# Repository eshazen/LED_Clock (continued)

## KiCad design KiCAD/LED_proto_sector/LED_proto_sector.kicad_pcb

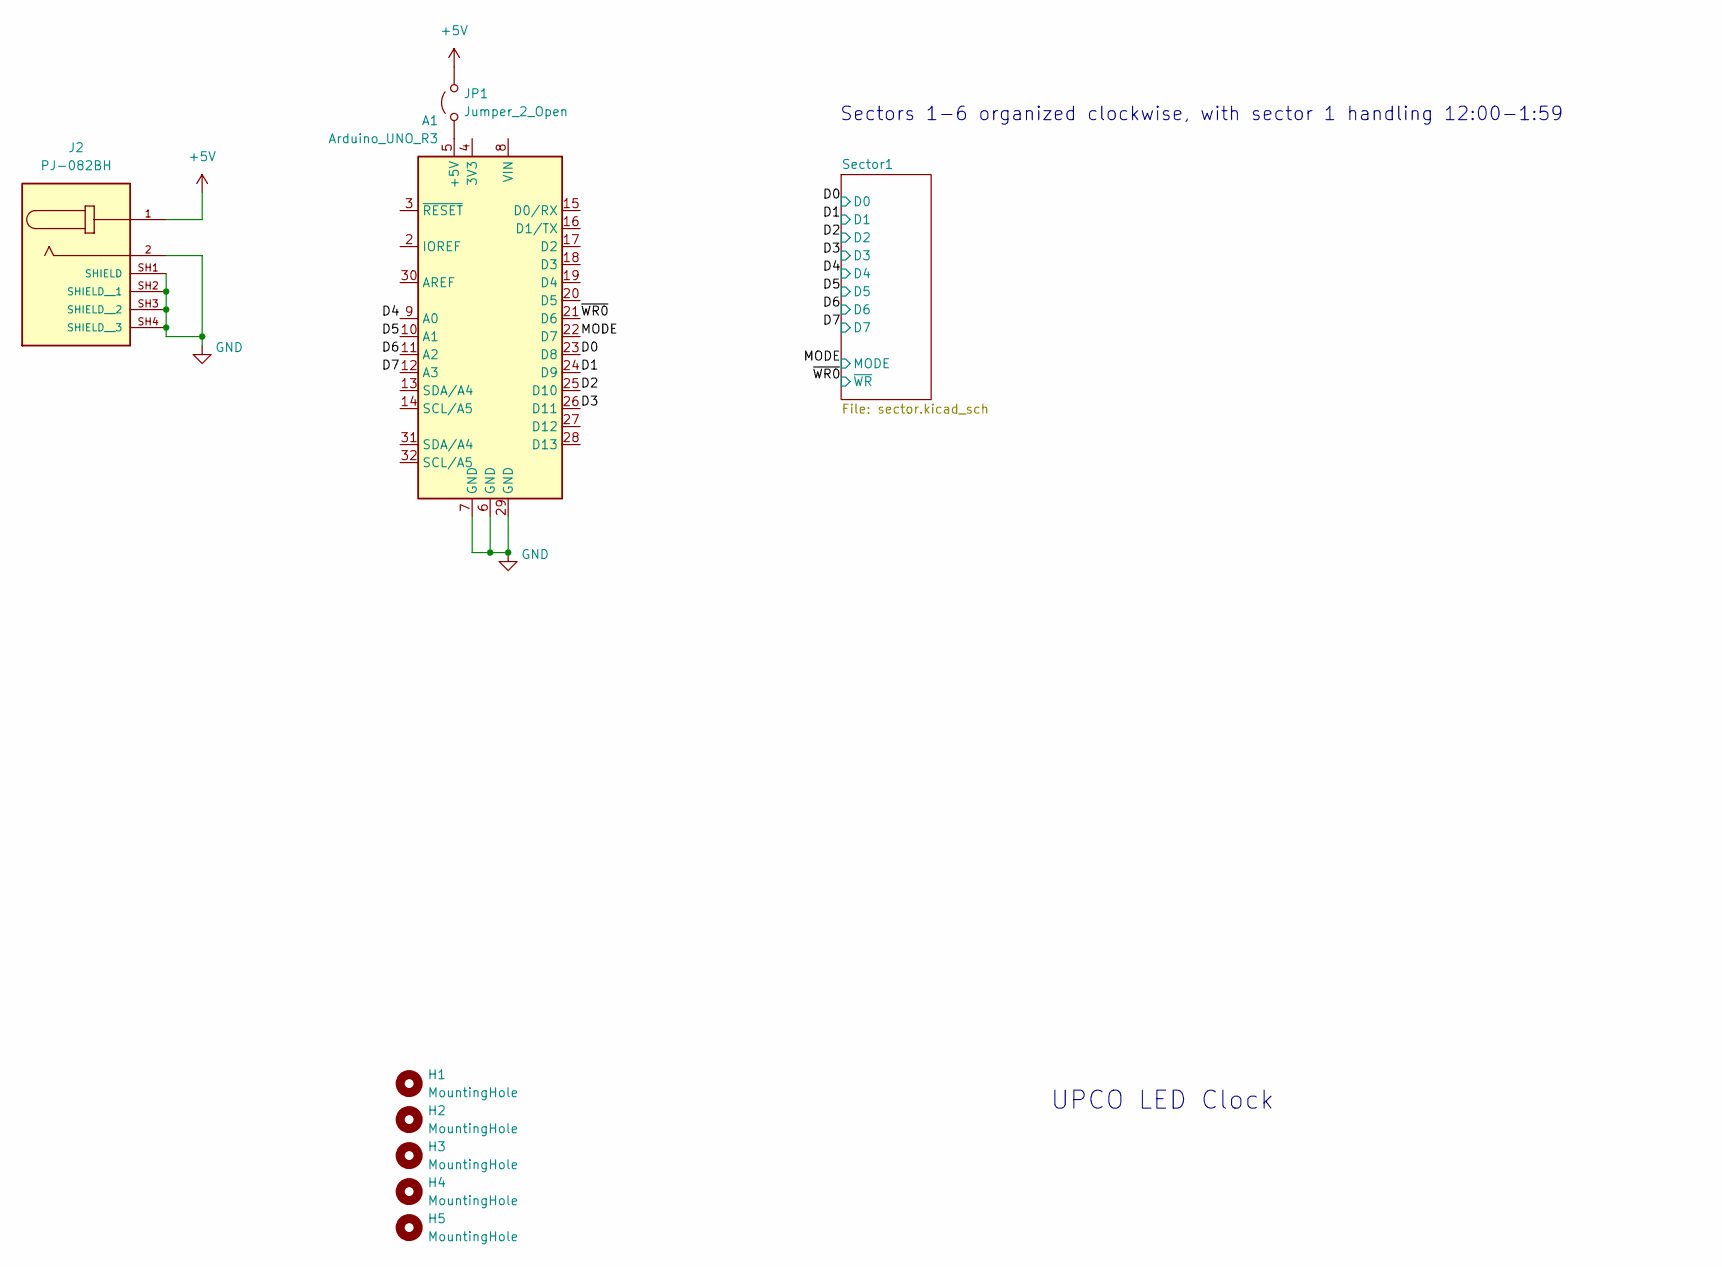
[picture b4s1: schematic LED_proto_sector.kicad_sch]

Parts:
A1: Arduino_UNO_R3
H1, H2, H3, H4, H5: MountingHole; MountingHole_4.3mm_M4
J2: PJ-082BH; SAMESKY_PJ-082BH; PARTREV 1.06
JP1: Jumper_2_Open; PinHeader_1x02_P2.54mm_Vertical

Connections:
+5V: J2.1, JP1.2 (B); also elsewhere on the board
/D0: A1.23 (D8); also elsewhere on the board
/D1: A1.24 (D9); also elsewhere on the board
/D2: A1.25 (D10); also elsewhere on the board
/D3: A1.26 (D11); also elsewhere on the board
/D4: A1.9 (A0); also elsewhere on the board
/D5: A1.10 (A1); also elsewhere on the board
/D6: A1.11 (A2); also elsewhere on the board
/D7: A1.12 (A3); also elsewhere on the board
/MODE: A1.22 (D7); also elsewhere on the board
/~WR0: A1.21 (D6); also elsewhere on the board
GND: A1.6 (GND), A1.7 (GND), A1.29 (GND), J2.2, J2.SH1 (SHIELD), J2.SH2 (SHIELD__1), J2.SH3 (SHIELD__2), J2.SH4 (SHIELD__3); also elsewhere on the board
unnamed: A1.5 (+5V), JP1.1 (A)

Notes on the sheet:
Sectors 1-6 organized clockwise, with sector 1 handling 12:00-1:59
UPCO LED Clock

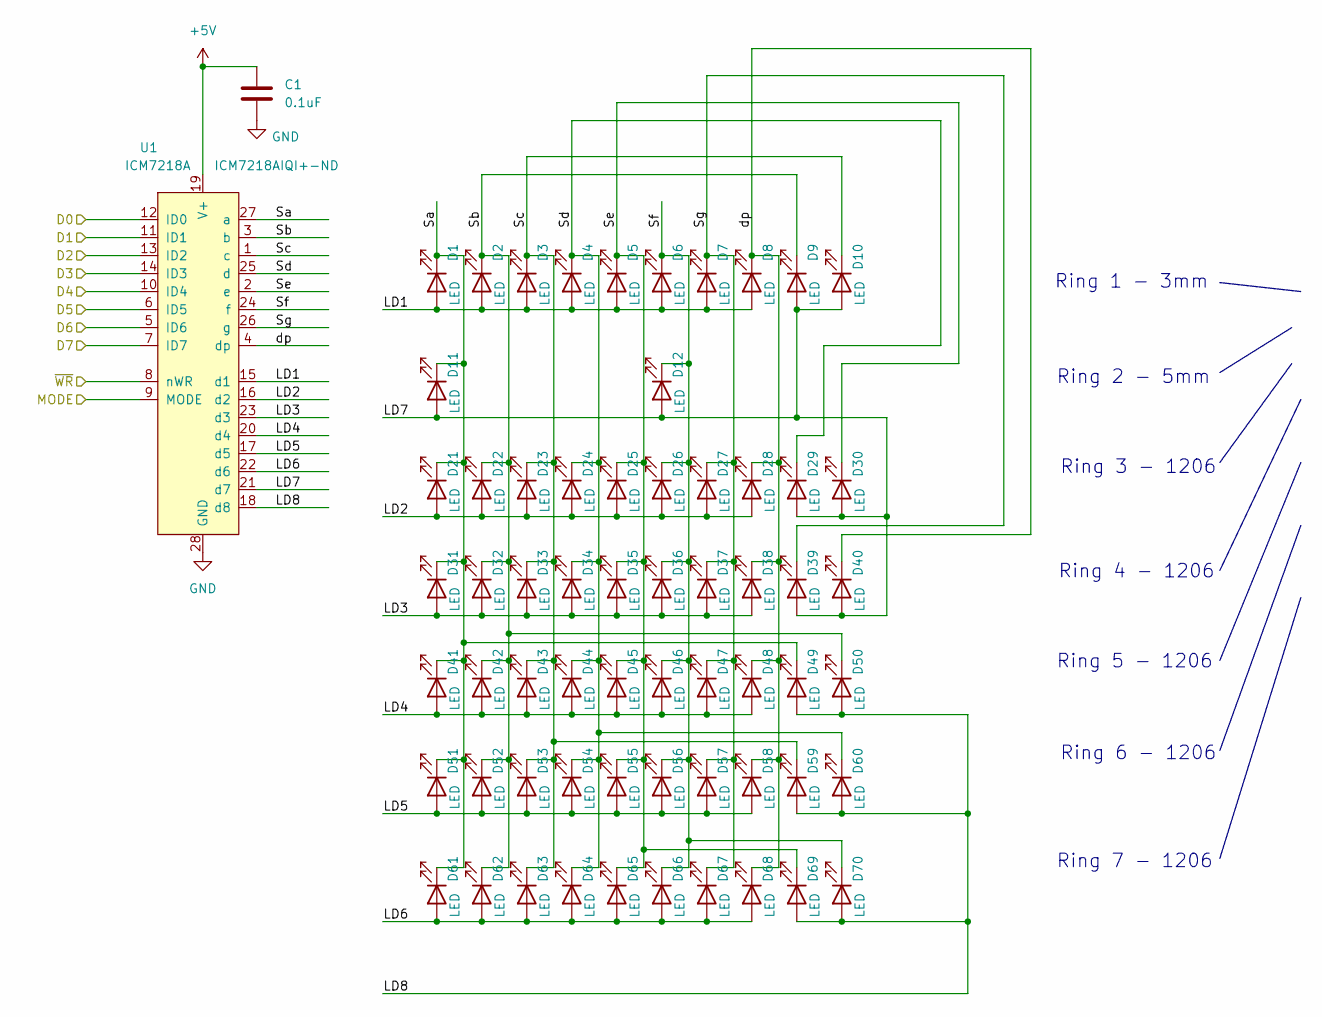
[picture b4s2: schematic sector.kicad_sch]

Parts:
C1: 0.1uF; C_1206_3216Metric_Pad1.33x1.80mm_HandSolder
D1, D2, D3, D4, D5, D6, D7, D8, D9, D10: LED; LED_D3.0mm
D11, D12: LED; LED_D5.0mm
D21, D22, D23, D24, D25, D26, D27, D28, D29, D30, D31, D32, D33, D34, D35, D36, D37, D38, D39, D40, D41, D42, D43, D44, D45, D46, D47, D48, D49, D50, D51, D52, D53, D54, D55, D56, D57, D58, D59, D60, D61, D62, D63, D64, D65, D66, D67, D68, D69, D70: LED; LED_1206_3216Metric_Pad1.42x1.75mm_HandSolder
U1: ICM7218A; DIP-28_W15.24mm_LongPads; DigiKey ICM7218AIQI+-ND

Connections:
+5V: C1.1, U1.19 (V+); also elsewhere on the board
/D0: U1.12 (ID0); also elsewhere on the board
/D1: U1.11 (ID1); also elsewhere on the board
/D2: U1.13 (ID2); also elsewhere on the board
/D3: U1.14 (ID3); also elsewhere on the board
/D4: U1.10 (ID4); also elsewhere on the board
/D5: U1.6 (ID5); also elsewhere on the board
/D6: U1.5 (ID6); also elsewhere on the board
/D7: U1.7 (ID7); also elsewhere on the board
/MODE: U1.9 (MODE); also elsewhere on the board
/Sector1/LD1: D1.2 (A), D2.2 (A), D3.2 (A), D4.2 (A), D5.2 (A), D6.2 (A), D7.2 (A), D8.2 (A), U1.15 (d1)
/Sector1/LD2: D21.2 (A), D22.2 (A), D23.2 (A), D24.2 (A), D25.2 (A), D26.2 (A), D27.2 (A), D28.2 (A), U1.16 (d2)
/Sector1/LD3: D31.2 (A), D32.2 (A), D33.2 (A), D34.2 (A), D35.2 (A), D36.2 (A), D37.2 (A), D38.2 (A), U1.23 (d3)
/Sector1/LD4: D41.2 (A), D42.2 (A), D43.2 (A), D44.2 (A), D45.2 (A), D46.2 (A), D47.2 (A), D48.2 (A), U1.20 (d4)
/Sector1/LD5: D51.2 (A), D52.2 (A), D53.2 (A), D54.2 (A), D55.2 (A), D56.2 (A), D57.2 (A), D58.2 (A), U1.17 (d5)
/Sector1/LD6: D61.2 (A), D62.2 (A), D63.2 (A), D64.2 (A), D65.2 (A), D66.2 (A), D67.2 (A), D68.2 (A), U1.22 (d6)
/Sector1/LD7: D9.2 (A), D10.2 (A), D11.2 (A), D12.2 (A), D29.2 (A), D30.2 (A), D39.2 (A), D40.2 (A), U1.21 (d7)
/Sector1/LD8: D49.2 (A), D50.2 (A), D59.2 (A), D60.2 (A), D69.2 (A), D70.2 (A), U1.18 (d8)
/Sector1/Sa: D1.1 (K), D11.1 (K), D21.1 (K), D31.1 (K), D41.1 (K), D49.1 (K), D51.1 (K), D61.1 (K), U1.27 (a)
/Sector1/Sb: D2.1 (K), D9.1 (K), D22.1 (K), D32.1 (K), D42.1 (K), D50.1 (K), D52.1 (K), D62.1 (K), U1.3 (b)
/Sector1/Sc: D3.1 (K), D10.1 (K), D23.1 (K), D33.1 (K), D43.1 (K), D53.1 (K), D59.1 (K), D63.1 (K), U1.1 (c)
/Sector1/Sd: D4.1 (K), D24.1 (K), D29.1 (K), D34.1 (K), D44.1 (K), D54.1 (K), D60.1 (K), D64.1 (K), U1.25 (d)
/Sector1/Se: D5.1 (K), D25.1 (K), D30.1 (K), D35.1 (K), D45.1 (K), D55.1 (K), D65.1 (K), D69.1 (K), U1.2 (e)
/Sector1/Sf: D6.1 (K), D12.1 (K), D26.1 (K), D36.1 (K), D46.1 (K), D56.1 (K), D66.1 (K), D70.1 (K), U1.24 (f)
/Sector1/Sg: D7.1 (K), D27.1 (K), D37.1 (K), D39.1 (K), D47.1 (K), D57.1 (K), D67.1 (K), U1.26 (g)
/Sector1/dp: D8.1 (K), D28.1 (K), D38.1 (K), D40.1 (K), D48.1 (K), D58.1 (K), D68.1 (K), U1.4 (dp)
/~WR0: U1.8 (nWR); also elsewhere on the board
GND: C1.2, U1.28 (GND); also elsewhere on the board

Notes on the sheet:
Ring 2 - 5mm
Ring 3 - 1206
Ring 4 - 1206
Ring 7 - 1206
Ring 6 - 1206
Ring 5 - 1206
Ring 1 - 3mm

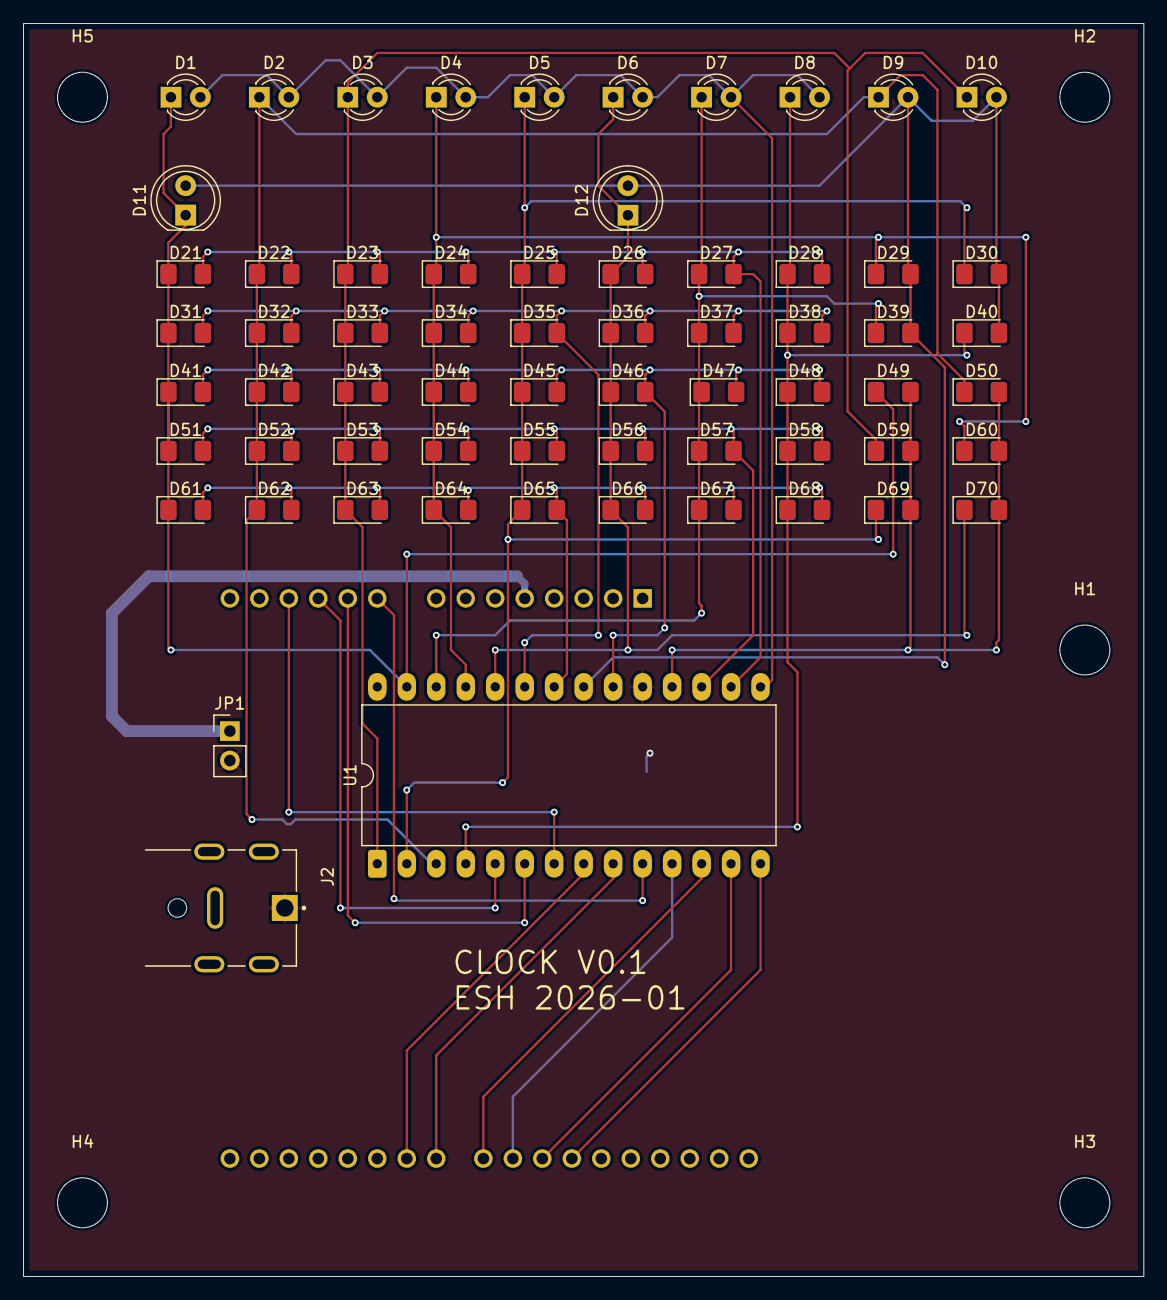
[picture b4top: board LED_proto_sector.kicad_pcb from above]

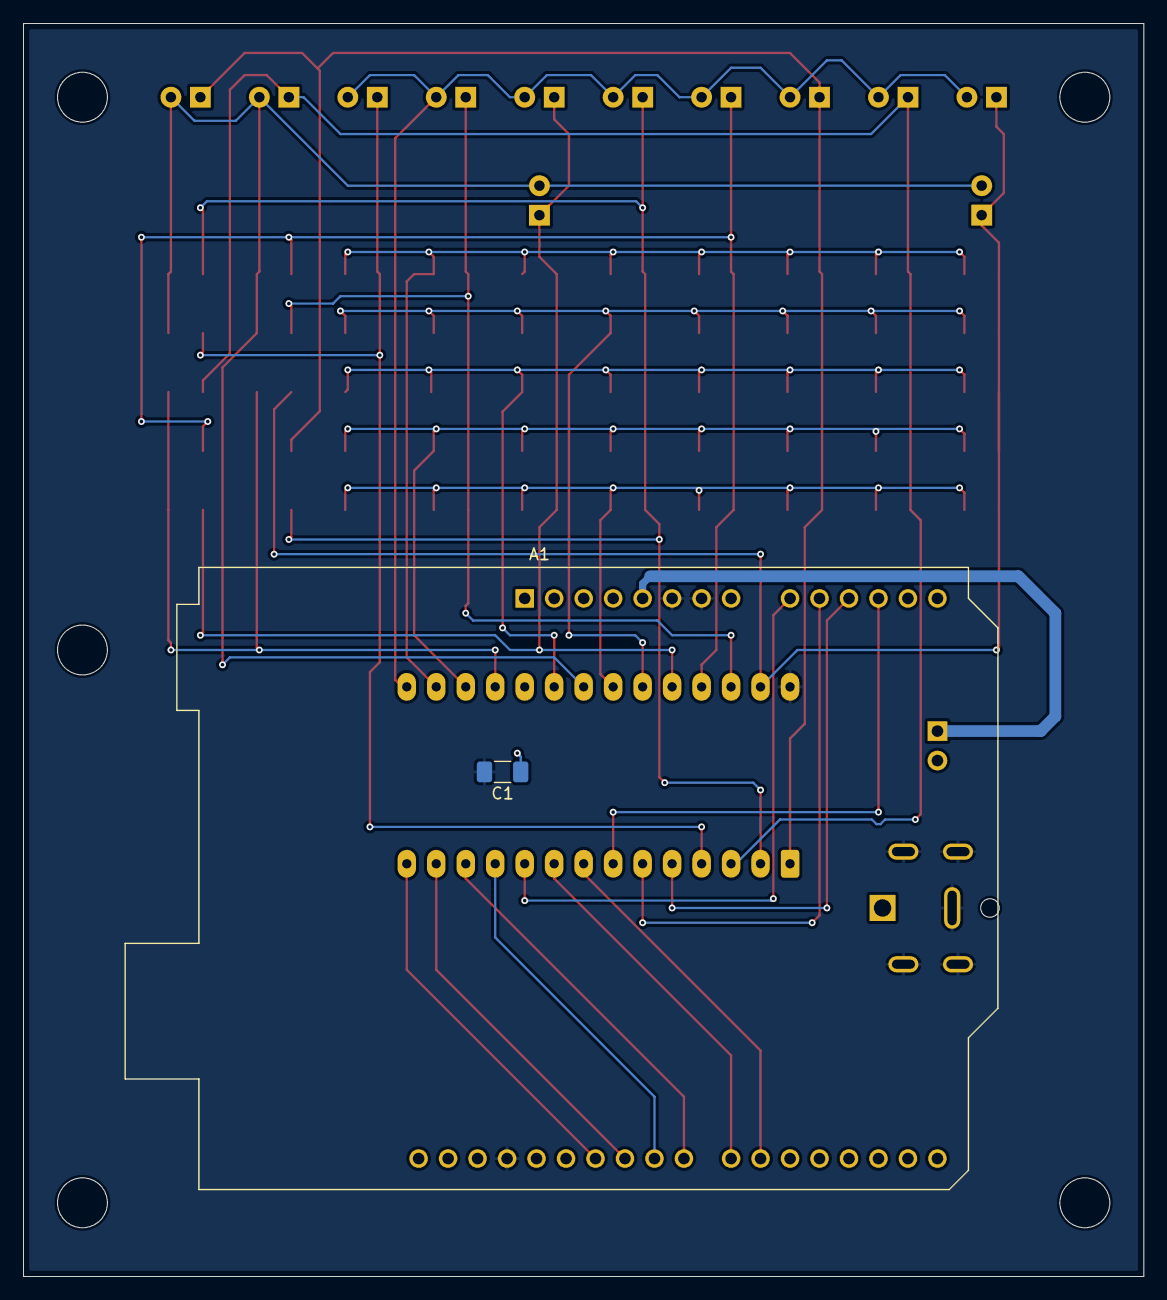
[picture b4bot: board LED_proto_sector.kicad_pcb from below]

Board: 2 copper layers, 96.5 x 108.0 mm, 72 parts (2 on the bottom side), 29 nets.

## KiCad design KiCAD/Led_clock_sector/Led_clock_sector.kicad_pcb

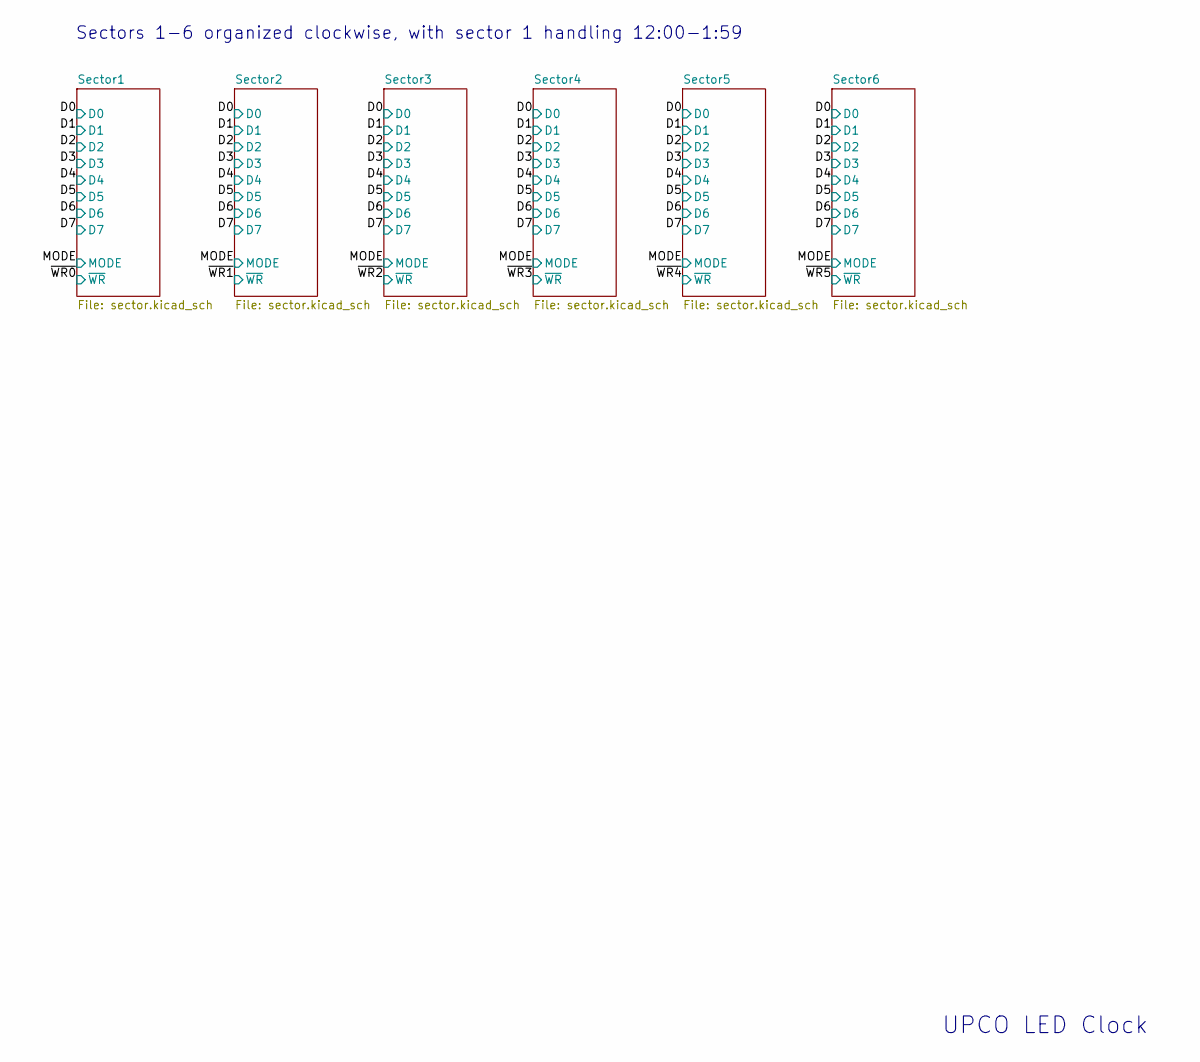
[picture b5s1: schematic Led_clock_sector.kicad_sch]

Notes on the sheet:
Sectors 1-6 organized clockwise, with sector 1 handling 12:00-1:59
UPCO LED Clock

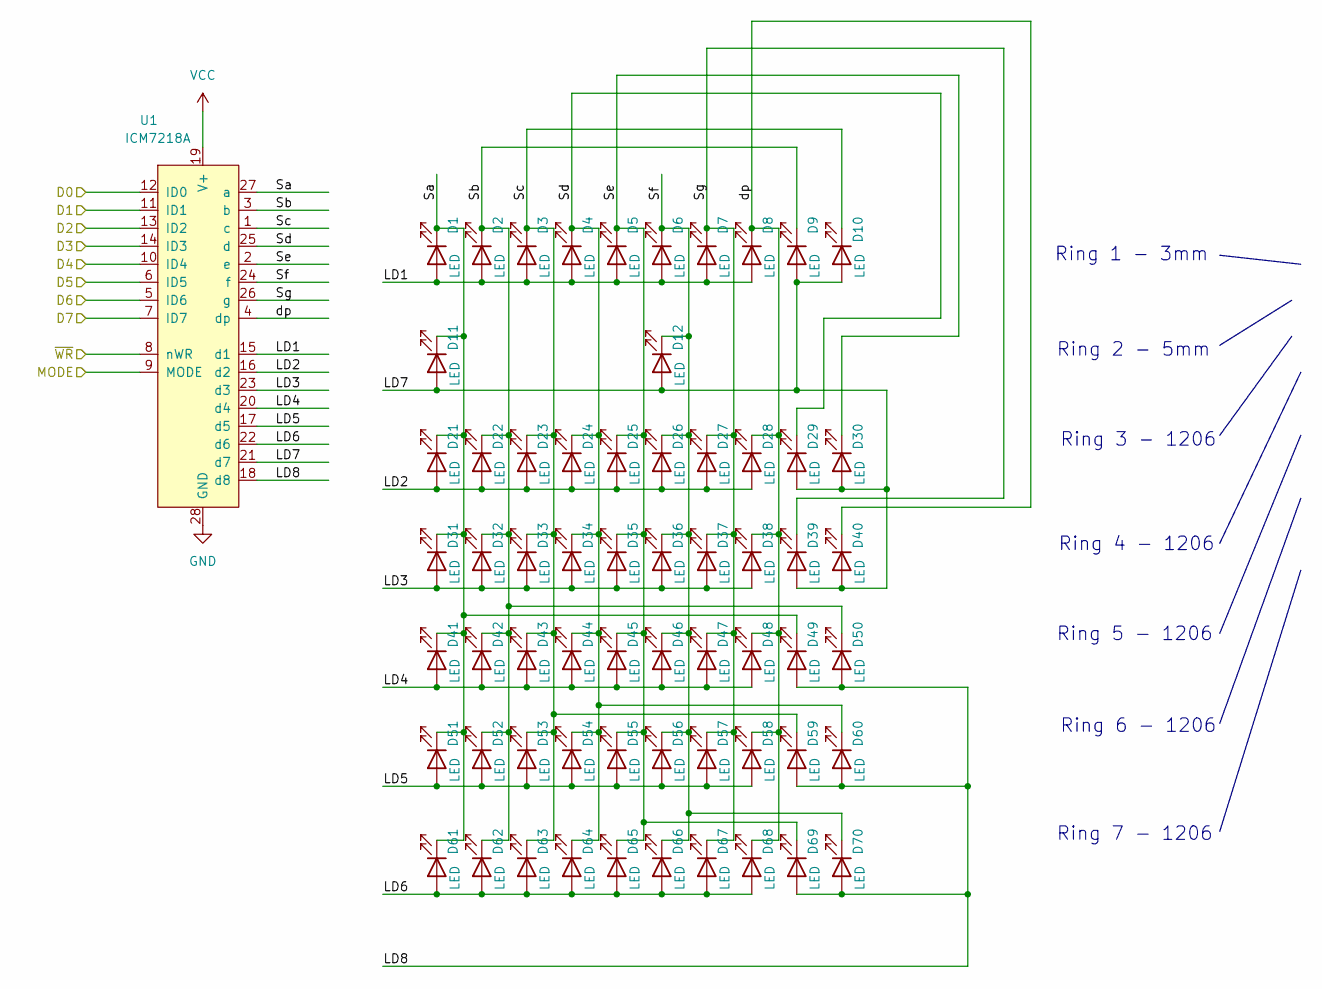
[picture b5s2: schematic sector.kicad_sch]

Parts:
D1, D2, D3, D4, D5, D6, D7, D8, D9, D10: LED; LED_D3.0mm
D11, D12: LED; LED_D5.0mm
D21, D22, D23, D24, D25, D26, D27, D28, D29, D30, D31, D32, D33, D34, D35, D36, D37, D38, D39, D40, D41, D42, D43, D44, D45, D46, D47, D48, D49, D50, D51, D52, D53, D54, D55, D56, D57, D58, D59, D60, D61, D62, D63, D64, D65, D66, D67, D68, D69, D70: LED; LED_1206_3216Metric_Pad1.42x1.75mm_HandSolder
U1: ICM7218A; PLCC-28

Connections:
/D0: U1.12 (ID0); also elsewhere on the board
/D1: U1.11 (ID1); also elsewhere on the board
/D2: U1.13 (ID2); also elsewhere on the board
/D3: U1.14 (ID3); also elsewhere on the board
/D4: U1.10 (ID4); also elsewhere on the board
/D5: U1.6 (ID5); also elsewhere on the board
/D6: U1.5 (ID6); also elsewhere on the board
/D7: U1.7 (ID7); also elsewhere on the board
/MODE: U1.9 (MODE); also elsewhere on the board
/Sector1/LD1: D1.2 (A), D2.2 (A), D3.2 (A), D4.2 (A), D5.2 (A), D6.2 (A), D7.2 (A), D8.2 (A), U1.15 (d1)
/Sector1/LD2: D21.2 (A), D22.2 (A), D23.2 (A), D24.2 (A), D25.2 (A), D26.2 (A), D27.2 (A), D28.2 (A), U1.16 (d2)
/Sector1/LD3: D31.2 (A), D32.2 (A), D33.2 (A), D34.2 (A), D35.2 (A), D36.2 (A), D37.2 (A), D38.2 (A), U1.23 (d3)
/Sector1/LD4: D41.2 (A), D42.2 (A), D43.2 (A), D44.2 (A), D45.2 (A), D46.2 (A), D47.2 (A), D48.2 (A), U1.20 (d4)
/Sector1/LD5: D51.2 (A), D52.2 (A), D53.2 (A), D54.2 (A), D55.2 (A), D56.2 (A), D57.2 (A), D58.2 (A), U1.17 (d5)
/Sector1/LD6: D61.2 (A), D62.2 (A), D63.2 (A), D64.2 (A), D65.2 (A), D66.2 (A), D67.2 (A), D68.2 (A), U1.22 (d6)
/Sector1/LD7: D9.2 (A), D10.2 (A), D11.2 (A), D12.2 (A), D29.2 (A), D30.2 (A), D39.2 (A), D40.2 (A), U1.21 (d7)
/Sector1/LD8: D49.2 (A), D50.2 (A), D59.2 (A), D60.2 (A), D69.2 (A), D70.2 (A), U1.18 (d8)
/Sector1/Sa: D1.1 (K), D11.1 (K), D21.1 (K), D31.1 (K), D41.1 (K), D49.1 (K), D51.1 (K), D61.1 (K), U1.27 (a)
/Sector1/Sb: D2.1 (K), D9.1 (K), D22.1 (K), D32.1 (K), D42.1 (K), D50.1 (K), D52.1 (K), D62.1 (K), U1.3 (b)
/Sector1/Sc: D3.1 (K), D10.1 (K), D23.1 (K), D33.1 (K), D43.1 (K), D53.1 (K), D59.1 (K), D63.1 (K), U1.1 (c)
/Sector1/Sd: D4.1 (K), D24.1 (K), D29.1 (K), D34.1 (K), D44.1 (K), D54.1 (K), D60.1 (K), D64.1 (K), U1.25 (d)
/Sector1/Se: D5.1 (K), D25.1 (K), D30.1 (K), D35.1 (K), D45.1 (K), D55.1 (K), D65.1 (K), D69.1 (K), U1.2 (e)
/Sector1/Sf: D6.1 (K), D12.1 (K), D26.1 (K), D36.1 (K), D46.1 (K), D56.1 (K), D66.1 (K), D70.1 (K), U1.24 (f)
/Sector1/Sg: D7.1 (K), D27.1 (K), D37.1 (K), D39.1 (K), D47.1 (K), D57.1 (K), D67.1 (K), U1.26 (g)
/Sector1/dp: D8.1 (K), D28.1 (K), D38.1 (K), D40.1 (K), D48.1 (K), D58.1 (K), D68.1 (K), U1.4 (dp)
/~WR0: U1.8 (nWR)
GND: U1.28 (GND); also elsewhere on the board
VCC: U1.19 (V+); also elsewhere on the board

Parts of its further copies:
D71, D72, D73, D74, D75, D76, D77, D78, D79, D80, D133, D134, D135, D136, D137, D138, D139, D140, D141, D142, D195, D196, D197, D198, D199, D200, D201, D202, D203, D204, D257, D258, D259, D260, D261, D262, D263, D264, D265, D266, D319, D320, D321, D322, D323, D324, D325, D326, D327, D328: LED; LED_D3.0mm
D81, D82, D143, D144, D205, D206, D267, D268, D329, D330: LED; LED_D5.0mm
D83, D84, D85, D86, D87, D88, D89, D90, D91, D92, D93, D94, D95, D96, D97, D98, D99, D100, D101, D102, D103, D104, D105, D106, D107, D108, D109, D110, D111, D112, D113, D114, D115, D116, D117, D118, D119, D120, D121, D122, D123, D124, D125, D126, D127, D128, D129, D130, D131, D132, D145, D146, D147, D148, D149, D150, D151, D152, D153, D154, D155, D156, D157, D158, D159, D160, D161, D162, D163, D164, D165, D166, D167, D168, D169, D170, D171, D172, D173, D174, D175, D176, D177, D178, D179, D180, D181, D182, D183, D184, D185, D186, D187, D188, D189, D190, D191, D192, D193, D194, D207, D208, D209, D210, D211, D212, D213, D214, D215, D216, D217, D218, D219, D220, D221, D222, D223, D224, D225, D226, D227, D228, D229, D230, D231, D232, D233, D234, D235, D236, D237, D238, D239, D240, D241, D242, D243, D244, D245, D246, D247, D248, D249, D250, D251, D252, D253, D254, D255, D256, D269, D270, D271, D272, D273, D274, D275, D276, D277, D278, D279, D280, D281, D282, D283, D284, D285, D286, D287, D288, D289, D290, D291, D292, D293, D294, D295, D296, D297, D298, D299, D300, D301, D302, D303, D304, D305, D306, D307, D308, D309, D310, D311, D312, D313, D314, D315, D316, D317, D318, D331, D332, D333, D334, D335, D336, D337, D338, D339, D340, D341, D342, D343, D344, D345, D346, D347, D348, D349, D350, D351, D352, D353, D354, D355, D356, D357, D358, D359, D360, D361, D362, D363, D364, D365, D366, D367, D368, D369, D370, D371, D372, D373, D374, D375, D376, D377, D378, D379, D380: LED; LED_1206_3216Metric_Pad1.42x1.75mm_HandSolder
U51, U52, U53, U54, U55: ICM7218A; PLCC-28

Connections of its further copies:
/D0: U51.12 (ID0), U52.12 (ID0), U53.12 (ID0), U54.12 (ID0), U55.12 (ID0); also elsewhere on the board
/D1: U51.11 (ID1), U52.11 (ID1), U53.11 (ID1), U54.11 (ID1), U55.11 (ID1); also elsewhere on the board
/D2: U51.13 (ID2), U52.13 (ID2), U53.13 (ID2), U54.13 (ID2), U55.13 (ID2); also elsewhere on the board
/D3: U51.14 (ID3), U52.14 (ID3), U53.14 (ID3), U54.14 (ID3), U55.14 (ID3); also elsewhere on the board
/D4: U51.10 (ID4), U52.10 (ID4), U53.10 (ID4), U54.10 (ID4), U55.10 (ID4); also elsewhere on the board
/D5: U51.6 (ID5), U52.6 (ID5), U53.6 (ID5), U54.6 (ID5), U55.6 (ID5); also elsewhere on the board
/D6: U51.5 (ID6), U52.5 (ID6), U53.5 (ID6), U54.5 (ID6), U55.5 (ID6); also elsewhere on the board
/D7: U51.7 (ID7), U52.7 (ID7), U53.7 (ID7), U54.7 (ID7), U55.7 (ID7); also elsewhere on the board
/MODE: U51.9 (MODE), U52.9 (MODE), U53.9 (MODE), U54.9 (MODE), U55.9 (MODE); also elsewhere on the board
/Sector2/LD1: D71.2 (A), D72.2 (A), D73.2 (A), D74.2 (A), D75.2 (A), D76.2 (A), D77.2 (A), D78.2 (A), U51.15 (d1)
/Sector2/LD2: D83.2 (A), D84.2 (A), D85.2 (A), D86.2 (A), D87.2 (A), D88.2 (A), D89.2 (A), D90.2 (A), U51.16 (d2)
/Sector2/LD3: D93.2 (A), D94.2 (A), D95.2 (A), D96.2 (A), D97.2 (A), D98.2 (A), D99.2 (A), D100.2 (A), U51.23 (d3)
/Sector2/LD4: D103.2 (A), D104.2 (A), D105.2 (A), D106.2 (A), D107.2 (A), D108.2 (A), D109.2 (A), D110.2 (A), U51.20 (d4)
/Sector2/LD5: D113.2 (A), D114.2 (A), D115.2 (A), D116.2 (A), D117.2 (A), D118.2 (A), D119.2 (A), D120.2 (A), U51.17 (d5)
/Sector2/LD6: D123.2 (A), D124.2 (A), D125.2 (A), D126.2 (A), D127.2 (A), D128.2 (A), D129.2 (A), D130.2 (A), U51.22 (d6)
/Sector2/LD7: D79.2 (A), D80.2 (A), D81.2 (A), D82.2 (A), D91.2 (A), D92.2 (A), D101.2 (A), D102.2 (A), U51.21 (d7)
/Sector2/LD8: D111.2 (A), D112.2 (A), D121.2 (A), D122.2 (A), D131.2 (A), D132.2 (A), U51.18 (d8)
/Sector2/Sa: D71.1 (K), D81.1 (K), D83.1 (K), D93.1 (K), D103.1 (K), D111.1 (K), D113.1 (K), D123.1 (K), U51.27 (a)
/Sector2/Sb: D72.1 (K), D79.1 (K), D84.1 (K), D94.1 (K), D104.1 (K), D112.1 (K), D114.1 (K), D124.1 (K), U51.3 (b)
/Sector2/Sc: D73.1 (K), D80.1 (K), D85.1 (K), D95.1 (K), D105.1 (K), D115.1 (K), D121.1 (K), D125.1 (K), U51.1 (c)
/Sector2/Sd: D74.1 (K), D86.1 (K), D91.1 (K), D96.1 (K), D106.1 (K), D116.1 (K), D122.1 (K), D126.1 (K), U51.25 (d)
/Sector2/Se: D75.1 (K), D87.1 (K), D92.1 (K), D97.1 (K), D107.1 (K), D117.1 (K), D127.1 (K), D131.1 (K), U51.2 (e)
/Sector2/Sf: D76.1 (K), D82.1 (K), D88.1 (K), D98.1 (K), D108.1 (K), D118.1 (K), D128.1 (K), D132.1 (K), U51.24 (f)
/Sector2/Sg: D77.1 (K), D89.1 (K), D99.1 (K), D101.1 (K), D109.1 (K), D119.1 (K), D129.1 (K), U51.26 (g)
/Sector2/dp: D78.1 (K), D90.1 (K), D100.1 (K), D102.1 (K), D110.1 (K), D120.1 (K), D130.1 (K), U51.4 (dp)
/Sector3/LD1: D133.2 (A), D134.2 (A), D135.2 (A), D136.2 (A), D137.2 (A), D138.2 (A), D139.2 (A), D140.2 (A), U52.15 (d1)
/Sector3/LD2: D145.2 (A), D146.2 (A), D147.2 (A), D148.2 (A), D149.2 (A), D150.2 (A), D151.2 (A), D152.2 (A), U52.16 (d2)
/Sector3/LD3: D155.2 (A), D156.2 (A), D157.2 (A), D158.2 (A), D159.2 (A), D160.2 (A), D161.2 (A), D162.2 (A), U52.23 (d3)
/Sector3/LD4: D165.2 (A), D166.2 (A), D167.2 (A), D168.2 (A), D169.2 (A), D170.2 (A), D171.2 (A), D172.2 (A), U52.20 (d4)
/Sector3/LD5: D175.2 (A), D176.2 (A), D177.2 (A), D178.2 (A), D179.2 (A), D180.2 (A), D181.2 (A), D182.2 (A), U52.17 (d5)
/Sector3/LD6: D185.2 (A), D186.2 (A), D187.2 (A), D188.2 (A), D189.2 (A), D190.2 (A), D191.2 (A), D192.2 (A), U52.22 (d6)
/Sector3/LD7: D141.2 (A), D142.2 (A), D143.2 (A), D144.2 (A), D153.2 (A), D154.2 (A), D163.2 (A), D164.2 (A), U52.21 (d7)
/Sector3/LD8: D173.2 (A), D174.2 (A), D183.2 (A), D184.2 (A), D193.2 (A), D194.2 (A), U52.18 (d8)
/Sector3/Sa: D133.1 (K), D143.1 (K), D145.1 (K), D155.1 (K), D165.1 (K), D173.1 (K), D175.1 (K), D185.1 (K), U52.27 (a)
/Sector3/Sb: D134.1 (K), D141.1 (K), D146.1 (K), D156.1 (K), D166.1 (K), D174.1 (K), D176.1 (K), D186.1 (K), U52.3 (b)
/Sector3/Sc: D135.1 (K), D142.1 (K), D147.1 (K), D157.1 (K), D167.1 (K), D177.1 (K), D183.1 (K), D187.1 (K), U52.1 (c)
/Sector3/Sd: D136.1 (K), D148.1 (K), D153.1 (K), D158.1 (K), D168.1 (K), D178.1 (K), D184.1 (K), D188.1 (K), U52.25 (d)
/Sector3/Se: D137.1 (K), D149.1 (K), D154.1 (K), D159.1 (K), D169.1 (K), D179.1 (K), D189.1 (K), D193.1 (K), U52.2 (e)
/Sector3/Sf: D138.1 (K), D144.1 (K), D150.1 (K), D160.1 (K), D170.1 (K), D180.1 (K), D190.1 (K), D194.1 (K), U52.24 (f)
/Sector3/Sg: D139.1 (K), D151.1 (K), D161.1 (K), D163.1 (K), D171.1 (K), D181.1 (K), D191.1 (K), U52.26 (g)
/Sector3/dp: D140.1 (K), D152.1 (K), D162.1 (K), D164.1 (K), D172.1 (K), D182.1 (K), D192.1 (K), U52.4 (dp)
/Sector4/LD1: D195.2 (A), D196.2 (A), D197.2 (A), D198.2 (A), D199.2 (A), D200.2 (A), D201.2 (A), D202.2 (A), U53.15 (d1)
/Sector4/LD2: D207.2 (A), D208.2 (A), D209.2 (A), D210.2 (A), D211.2 (A), D212.2 (A), D213.2 (A), D214.2 (A), U53.16 (d2)
/Sector4/LD3: D217.2 (A), D218.2 (A), D219.2 (A), D220.2 (A), D221.2 (A), D222.2 (A), D223.2 (A), D224.2 (A), U53.23 (d3)
/Sector4/LD4: D227.2 (A), D228.2 (A), D229.2 (A), D230.2 (A), D231.2 (A), D232.2 (A), D233.2 (A), D234.2 (A), U53.20 (d4)
/Sector4/LD5: D237.2 (A), D238.2 (A), D239.2 (A), D240.2 (A), D241.2 (A), D242.2 (A), D243.2 (A), D244.2 (A), U53.17 (d5)
/Sector4/LD6: D247.2 (A), D248.2 (A), D249.2 (A), D250.2 (A), D251.2 (A), D252.2 (A), D253.2 (A), D254.2 (A), U53.22 (d6)
/Sector4/LD7: D203.2 (A), D204.2 (A), D205.2 (A), D206.2 (A), D215.2 (A), D216.2 (A), D225.2 (A), D226.2 (A), U53.21 (d7)
/Sector4/LD8: D235.2 (A), D236.2 (A), D245.2 (A), D246.2 (A), D255.2 (A), D256.2 (A), U53.18 (d8)
/Sector4/Sa: D195.1 (K), D205.1 (K), D207.1 (K), D217.1 (K), D227.1 (K), D235.1 (K), D237.1 (K), D247.1 (K), U53.27 (a)
/Sector4/Sb: D196.1 (K), D203.1 (K), D208.1 (K), D218.1 (K), D228.1 (K), D236.1 (K), D238.1 (K), D248.1 (K), U53.3 (b)
/Sector4/Sc: D197.1 (K), D204.1 (K), D209.1 (K), D219.1 (K), D229.1 (K), D239.1 (K), D245.1 (K), D249.1 (K), U53.1 (c)
/Sector4/Sd: D198.1 (K), D210.1 (K), D215.1 (K), D220.1 (K), D230.1 (K), D240.1 (K), D246.1 (K), D250.1 (K), U53.25 (d)
/Sector4/Se: D199.1 (K), D211.1 (K), D216.1 (K), D221.1 (K), D231.1 (K), D241.1 (K), D251.1 (K), D255.1 (K), U53.2 (e)
/Sector4/Sf: D200.1 (K), D206.1 (K), D212.1 (K), D222.1 (K), D232.1 (K), D242.1 (K), D252.1 (K), D256.1 (K), U53.24 (f)
/Sector4/Sg: D201.1 (K), D213.1 (K), D223.1 (K), D225.1 (K), D233.1 (K), D243.1 (K), D253.1 (K), U53.26 (g)
/Sector4/dp: D202.1 (K), D214.1 (K), D224.1 (K), D226.1 (K), D234.1 (K), D244.1 (K), D254.1 (K), U53.4 (dp)
/Sector5/LD1: D257.2 (A), D258.2 (A), D259.2 (A), D260.2 (A), D261.2 (A), D262.2 (A), D263.2 (A), D264.2 (A), U54.15 (d1)
/Sector5/LD2: D269.2 (A), D270.2 (A), D271.2 (A), D272.2 (A), D273.2 (A), D274.2 (A), D275.2 (A), D276.2 (A), U54.16 (d2)
/Sector5/LD3: D279.2 (A), D280.2 (A), D281.2 (A), D282.2 (A), D283.2 (A), D284.2 (A), D285.2 (A), D286.2 (A), U54.23 (d3)
/Sector5/LD4: D289.2 (A), D290.2 (A), D291.2 (A), D292.2 (A), D293.2 (A), D294.2 (A), D295.2 (A), D296.2 (A), U54.20 (d4)
/Sector5/LD5: D299.2 (A), D300.2 (A), D301.2 (A), D302.2 (A), D303.2 (A), D304.2 (A), D305.2 (A), D306.2 (A), U54.17 (d5)
/Sector5/LD6: D309.2 (A), D310.2 (A), D311.2 (A), D312.2 (A), D313.2 (A), D314.2 (A), D315.2 (A), D316.2 (A), U54.22 (d6)
/Sector5/LD7: D265.2 (A), D266.2 (A), D267.2 (A), D268.2 (A), D277.2 (A), D278.2 (A), D287.2 (A), D288.2 (A), U54.21 (d7)
/Sector5/LD8: D297.2 (A), D298.2 (A), D307.2 (A), D308.2 (A), D317.2 (A), D318.2 (A), U54.18 (d8)
/Sector5/Sa: D257.1 (K), D267.1 (K), D269.1 (K), D279.1 (K), D289.1 (K), D297.1 (K), D299.1 (K), D309.1 (K), U54.27 (a)
/Sector5/Sb: D258.1 (K), D265.1 (K), D270.1 (K), D280.1 (K), D290.1 (K), D298.1 (K), D300.1 (K), D310.1 (K), U54.3 (b)
/Sector5/Sc: D259.1 (K), D266.1 (K), D271.1 (K), D281.1 (K), D291.1 (K), D301.1 (K), D307.1 (K), D311.1 (K), U54.1 (c)
/Sector5/Sd: D260.1 (K), D272.1 (K), D277.1 (K), D282.1 (K), D292.1 (K), D302.1 (K), D308.1 (K), D312.1 (K), U54.25 (d)
/Sector5/Se: D261.1 (K), D273.1 (K), D278.1 (K), D283.1 (K), D293.1 (K), D303.1 (K), D313.1 (K), D317.1 (K), U54.2 (e)
/Sector5/Sf: D262.1 (K), D268.1 (K), D274.1 (K), D284.1 (K), D294.1 (K), D304.1 (K), D314.1 (K), D318.1 (K), U54.24 (f)
/Sector5/Sg: D263.1 (K), D275.1 (K), D285.1 (K), D287.1 (K), D295.1 (K), D305.1 (K), D315.1 (K), U54.26 (g)
/Sector5/dp: D264.1 (K), D276.1 (K), D286.1 (K), D288.1 (K), D296.1 (K), D306.1 (K), D316.1 (K), U54.4 (dp)
/Sector6/LD1: D319.2 (A), D320.2 (A), D321.2 (A), D322.2 (A), D323.2 (A), D324.2 (A), D325.2 (A), D326.2 (A), U55.15 (d1)
/Sector6/LD2: D331.2 (A), D332.2 (A), D333.2 (A), D334.2 (A), D335.2 (A), D336.2 (A), D337.2 (A), D338.2 (A), U55.16 (d2)
/Sector6/LD3: D341.2 (A), D342.2 (A), D343.2 (A), D344.2 (A), D345.2 (A), D346.2 (A), D347.2 (A), D348.2 (A), U55.23 (d3)
/Sector6/LD4: D351.2 (A), D352.2 (A), D353.2 (A), D354.2 (A), D355.2 (A), D356.2 (A), D357.2 (A), D358.2 (A), U55.20 (d4)
/Sector6/LD5: D361.2 (A), D362.2 (A), D363.2 (A), D364.2 (A), D365.2 (A), D366.2 (A), D367.2 (A), D368.2 (A), U55.17 (d5)
/Sector6/LD6: D371.2 (A), D372.2 (A), D373.2 (A), D374.2 (A), D375.2 (A), D376.2 (A), D377.2 (A), D378.2 (A), U55.22 (d6)
/Sector6/LD7: D327.2 (A), D328.2 (A), D329.2 (A), D330.2 (A), D339.2 (A), D340.2 (A), D349.2 (A), D350.2 (A), U55.21 (d7)
/Sector6/LD8: D359.2 (A), D360.2 (A), D369.2 (A), D370.2 (A), D379.2 (A), D380.2 (A), U55.18 (d8)
/Sector6/Sa: D319.1 (K), D329.1 (K), D331.1 (K), D341.1 (K), D351.1 (K), D359.1 (K), D361.1 (K), D371.1 (K), U55.27 (a)
/Sector6/Sb: D320.1 (K), D327.1 (K), D332.1 (K), D342.1 (K), D352.1 (K), D360.1 (K), D362.1 (K), D372.1 (K), U55.3 (b)
/Sector6/Sc: D321.1 (K), D328.1 (K), D333.1 (K), D343.1 (K), D353.1 (K), D363.1 (K), D369.1 (K), D373.1 (K), U55.1 (c)
/Sector6/Sd: D322.1 (K), D334.1 (K), D339.1 (K), D344.1 (K), D354.1 (K), D364.1 (K), D370.1 (K), D374.1 (K), U55.25 (d)
/Sector6/Se: D323.1 (K), D335.1 (K), D340.1 (K), D345.1 (K), D355.1 (K), D365.1 (K), D375.1 (K), D379.1 (K), U55.2 (e)
/Sector6/Sf: D324.1 (K), D330.1 (K), D336.1 (K), D346.1 (K), D356.1 (K), D366.1 (K), D376.1 (K), D380.1 (K), U55.24 (f)
/Sector6/Sg: D325.1 (K), D337.1 (K), D347.1 (K), D349.1 (K), D357.1 (K), D367.1 (K), D377.1 (K), U55.26 (g)
/Sector6/dp: D326.1 (K), D338.1 (K), D348.1 (K), D350.1 (K), D358.1 (K), D368.1 (K), D378.1 (K), U55.4 (dp)
/~WR1: U51.8 (nWR)
/~WR2: U52.8 (nWR)
/~WR3: U53.8 (nWR)
/~WR4: U54.8 (nWR)
/~WR5: U55.8 (nWR)
GND: U51.28 (GND), U52.28 (GND), U53.28 (GND), U54.28 (GND), U55.28 (GND); also elsewhere on the board
VCC: U51.19 (V+), U52.19 (V+), U53.19 (V+), U54.19 (V+), U55.19 (V+); also elsewhere on the board

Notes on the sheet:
Ring 2 - 5mm
Ring 3 - 1206
Ring 4 - 1206
Ring 7 - 1206
Ring 6 - 1206
Ring 5 - 1206
Ring 1 - 3mm

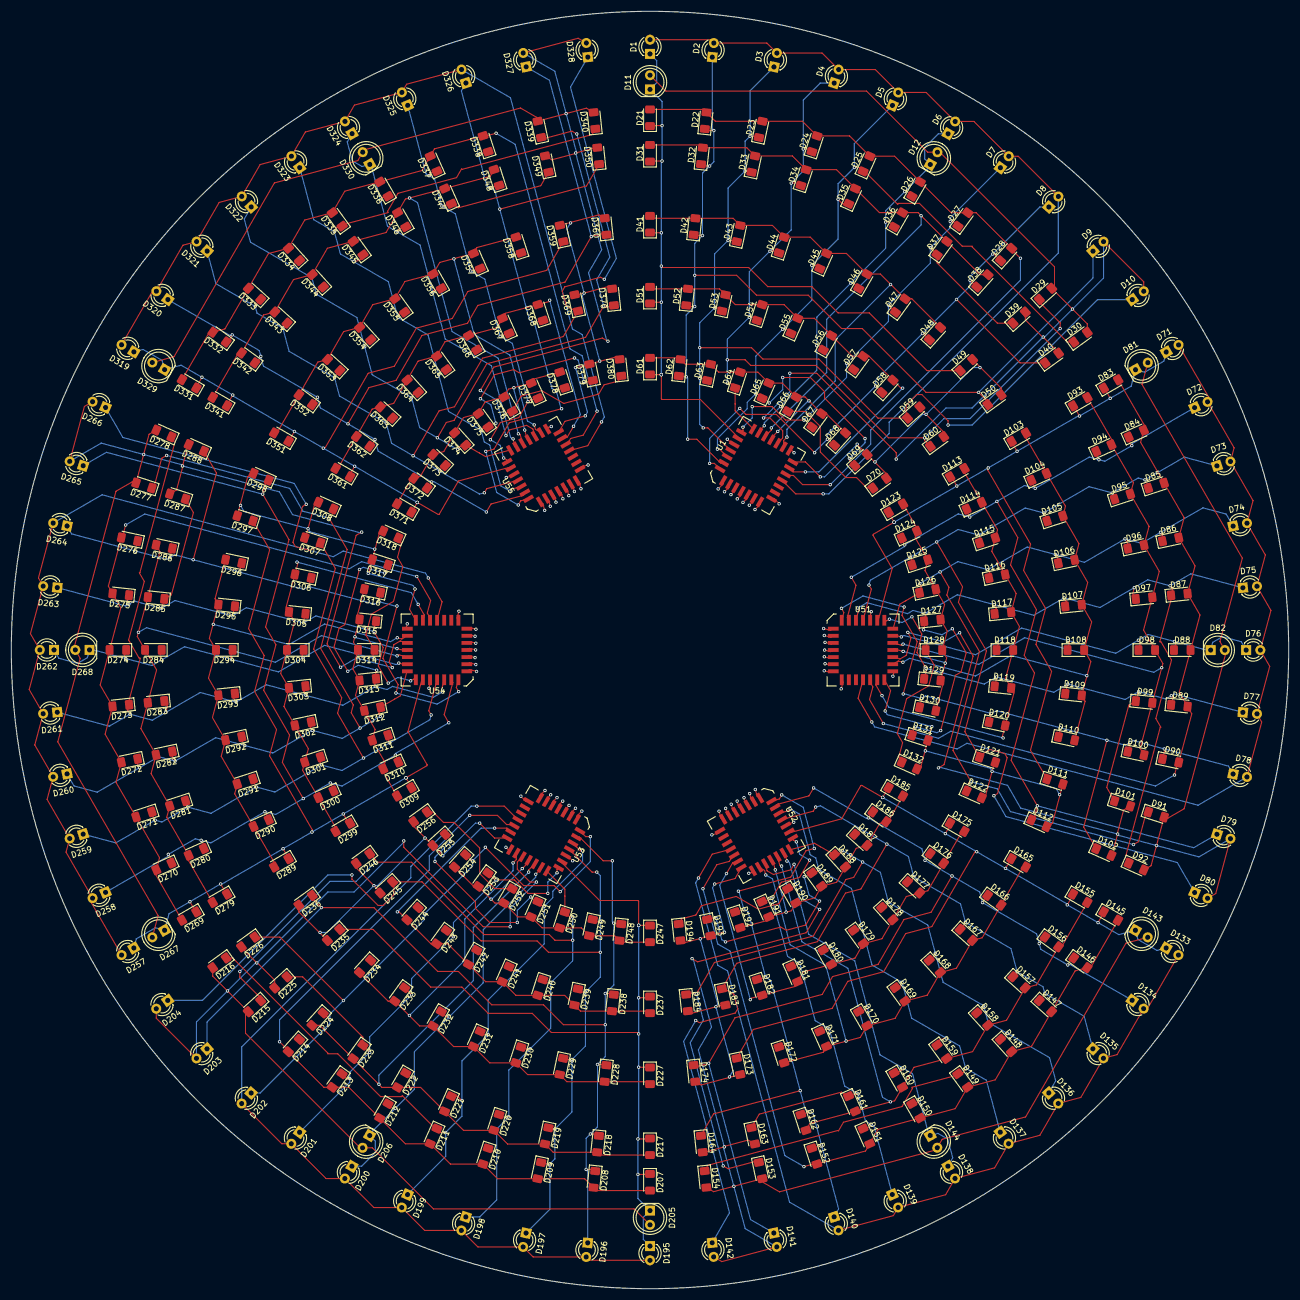
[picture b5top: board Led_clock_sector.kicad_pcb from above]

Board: 2 copper layers, 228.6 x 228.6 mm, 378 parts (0 on the bottom side), 107 nets.
